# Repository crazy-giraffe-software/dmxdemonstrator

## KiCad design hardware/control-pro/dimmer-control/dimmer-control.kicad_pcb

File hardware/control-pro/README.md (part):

# DMX Demonstrator Control Pro  (DMX-CP*)

## Overview

The control-pro is built to work with either transmitter or transmitter-retro. When used with an Arduino, an additional board, the DMX-TX2, is required to connect the control-pro to the Arduino. The transmitter software automatically detects whether DMX-TX1, the standard transmitter, or DMX-TX2, the control-pro adapter, is connected.

The control pro is designed so that a series of components are sandwiched between 2 circuit boards. As a result, the heights of the components are fairly sensitive in order to make things line up nicely. Here are the parts for which I designed. The DMX-CPDB and DMX-CPCB boards contains all the parts and are the bottom of the sandwich, the DMX-CPDF and DMX-CPCB are the faceplate, i.e. the tops of the sandwich. If you are wondering why there are 4 total boards, see _PCB->Quality vs Price_ below.

## Online parts list

Sparkfun offers some, but not all, of the components required for the Control Pro. For the parts they can supply, you can find a parts lists [here](https://www.sparkfun.com/wish_lists/160543).

Additionally, you'll need some parts from the common parts lists as well. You can find the common parts list [here](https://www.sparkfun.com/wish_lists/160406). The rainbow LED pack include 2 sets of LED so if you are building more than 2 transmitters or receivers, make sure to buy 1 pack for every 2 transmitters/receivers.

## PCB

You can order the PCBs from [OHS Park](https://oshpark.com/):

- [Clock Control: DMX-CPCB 1.3](https://oshpark.com/shared_projects/???)
- [Clock Faceplate: DMX-CPCF 1.3](https://oshpark.com/shared_projects/???)
- [Dimmer Control: DMX-CPDB 1.3](https://oshpark.com/shared_projects/???)
- [Dimmer Faceplate: DMX-CPDF 1.3](https://oshpark.com/shared_projects/???)

### Quality vs Price

While it is counterintuitive (and in some cases wrong), splitting the clock controls and dimmer controls on different boards reduces cost. Many PCB manufacturers offer a fixed cost for board smaller than a certain size. These boards are 100mm x 100mm, which is standard max size for many low-cost board manufacturers. Others like OHSPark charge by the square inch and therefore the separate control approach is more expensive. Rev 1.1 was a single set of boards 180mm x 90mm for which OHSPark charges about $250US for 3 copies of both boards. Rev 1.3 is more expensive from OHSPark but can be as cheap as $20US for 5 copies of all 4 boards from cheaper board manufacturers. Yes, there is a quality BIG difference between those prices but the cheaper board will work just fine.

OHSPark offers really great quality at great prices, they are easy to work with, manufacture 100% in the US, and their support is excellent. I use OHSPark for almost everything I build, expect when the cost is super high. Lower cost boards can be had but if you spec the same quality board OHSPark offers at those places, you will find OHSPark to be competitive. Yes, the links above are for the more expensive OHSPark board for the reason I listed above plus ease of use: You can upload the file directly from Kicad and they can produce a board. Better yet, they will save that board for others to order. They make it so easy to order for a project like this it's silly not to use them.

I offer this opinion freely and do not receive any compensation from OHSPark.

## Parts

The Control Pro is designed so that a series of components are sandwiched between 2 circuit boards. As a result, the heights of the components are fairly sensitive in order to make things line up nicely. Here are the parts for which I designed. The DMX-CPDB and DMX-CPCB boards contains all the parts and are the bottom of the sandwich, the DMX-CPDF and DMX-CPCB are the faceplate, i.e. the tops of the sandwich. If you are wondering why there are 4 total boards, see _PCB->Quality vs Price_.

### Slider Potentiometers

Getting a potentiometer and knob combo that would work with the rest of the components was probably the hardest part of part selection.
I had initially ordered some 60mm 10k sliders from SparkFun with matching knobs and they measures about 25mm from the bottom of the
part to the bottom of the knob, which is way too tall for the other components! I landed on a combination of Bourns PTA Series
sliders with an knob available from Sparkfun (and others). During this process, I opted for a 45mm travel to keep the board smaller/cheaper
while still offering good mechanical resolution. The specific parts I designed for are:

- Dimmer Sliders: Bournes PTA4543-2015DPB103, quantity 4:
  - [Data sheet](https://www.mouser.com/datasheet/2/54/pta-778345.pdf)
  - [Digikey PTA4543-2015DPB103-ND](https://www.digikey.com/products/en?keywords=PTA4543-2015DPB103-ND)
  - [Mouser 652-PTA45432015DPB10](https://www.mouser.com/ProductDetail/Bourns/PTA4543-2015DPB103?qs=U%2FacTlguYxbmwS%2FtylIWJw%3D%3D)
- Knobs: Eagle 450-3051, quantity 4:
  - [Datasheet](https://www.mouser.com/datasheet/2/209/EPD-200140-1171100.pdf)
  - [Mouser 450-3051](https://www.mouser.com/ProductDetail/Eagle-Plastic-Devices/450-3051?qs=hTs5c5NaUrTeABpuQnP9ug%3D%3D)
  - [Sparkfun COM-09120](https://www.sparkfun.com/products/9120) - Included in online parts list

### Toggle Switches

Just about any miniature toggle switch will do, many manufacturers make a switch in a similar size. I specifically used the E-Switch Series 100 Miniature Toggle Switches, specifically:

- Clock Speed: E-Switch 100DP3T1B1M1QEH, quantity 1:
  - [Datasheet](https://sten-eswitch-13110800-production.s3.amazonaws.com/system/asset/product_line/data_sheet/129/100.pdf)
  - [Digikey EG2413-ND](https://www.digikey.com/products/en?keywords=100DP3T1B1M1QEH)
  - [Mouser 612-100-H1111](https://www.mouser.com/ProductDetail/E-Switch/100DP3T1B1M1QEH?qs=g8hxKYs5b3yy1L1GZVrx5w%3D%3D)
- Clock Step: E-Switch 100SP2T1B1M1QEH, quantity 1:
  - [Datasheet](https://sten-eswitch-13110800-production.s3.amazonaws.com/system/asset/product_line/data_sheet/129/100.pdf)
  - [Digikey EG2373-ND](https://www.digikey.com/product-detail/en/e-switch/100SP2T1B1M1QEH/EG2373-ND/378842)
  - [Mouser 612-100-B1111](https://www.mouser.com/ProductDetail/E-Switch/100SP2T1B1M1QEH?qs=HKd%2Fp3M7KlWCZ%252BGqDexPKQ%3D%3D)

### Rotary Potentiometer

With the toggle and sliders determining the basic component height, I searched for a rotary potentiometer to fit the requirements and once again found a Bournes product. It has a 6mm "D"/flattened shaft so just about any 6mm flattened shaft knob will work but something with a set screw will help secure it. I did not find a great choice at Digikey or Mouser but Amazon and EBay has a ton of choices, designed for use with musical instruments.

Sparkfun offers a potentiometer and knob that make an excellent choice. The knob even [goes to 11](https://en.wikipedia.org/wiki/Up_to_eleven). The Sparkfun part is not a Bournes PTV09A-4030F-B103 but it's the same physical size and resistance.

Specifically:

- Clock Speed Control: Bournes PTV09A-4030F-B103, quantity 1:
  - [Datasheet](https://www.bourns.com/docs/Product-Datasheets/PTV09.pdf)
  - [Digikey 118-PTV09A-4030F-B103-ND](https://www.digikey.com/en/products/detail/bourns-inc/PTV09A-4030F-B103/3820581)
  - [Mouser 652-PTV09A-4030FB103](https://www.mouser.com/ProductDetail/Bourns/PTV09A-4030F-B103?qs=Zq5ylnUbLm4pfFuWlwC80Q%3D%3D)
  - [Sparkfun COM-09288](https://www.sparkfun.com/products/9288) - Included in online parts list
- Knob, quantity 1:
  - [Sparkfun COM-11951](https://www.sparkfun.com/products/11951) - Included in online parts list

### LEDs and Spacers

Luckily most LEDs have leads long enough to make it from the bottom to top board so nothing special is needed here, just make sure to have 17.5mm of lead length. Most LEDs have a voltage and current range near 2v and 10ma and the design will accommodate variances easily.

I like the [Sparkfun rainbow LED Kit](https://www.sparkfun.com/products/12903) which gives you 2 each of 6 colors, letting you match colors for dimmers 1-4, data and clock on both the transmitter and receiver without re-using colors. This LED kit is included in the common parts list. However, they will need a bit of added stability, which is where an LED spacer is needed. Something between 16mm and 17mm will work fine. Here's a suitable one:

- LED: T1 3/4 or 5mm Led in various colors, quantity 1:
  - [Sparkfun rainbow LED Kit](https://www.sparkfun.com/products/12903) - Included in common online parts list
- LED Spacer: Würth 705820170, quantity 8:
  - [Data sheet](https://www.we-online.de/katalog/datasheet/705820xxx_overview.pdf)
  - [Digikey 732-11617-ND](https://www.digikey.com/product-detail/en/w%C3%BCrth-elektronik/705820170/732-11617-ND/7681962)
  - [Mouser 710-705820170](https://www.mouser.com/ProductDetail/Wurth-Elektronik/705820170?qs=wr8lucFkNMUaK6Cwpwjx5Q%3D%3D)

The rainbow LED kit includes 1 red and one green LED for the data and clock. However, there are 3 sets of data and clock LEDs on the three boards. Also, there are 2 LEDs to verify detection of the control-pro, one on each board. These LEDs are included in the control-pro online parts list [here](https://www.sparkfun.com/wish_lists/160543).

### Cable and Connector

To connect the controller to the transmitter, you'll need some cables and connectors. Ribbon cable makes a nice choice for this and you can find pre-made ribbon cable assemblies on Amazon and EBay easily. I've designed for a 16 pin cable. I recommend shrouded headers for connecting to PCBs and it ensures you don't plug the cable in backwards. Here are some suitable headers:

- Header: Würth Elektronik 61201621721, quantity 4:
  - [Datasheet](https://www.we-online.com/components/products/datasheet/61201621721.pdf)
  - [Digikey 732-2099-ND](https://www.digikey.com/en/products/detail/w%C3%BCrth-elektronik/61201621721/2060595)
  - [Mouser 710-61201621721](https://www.mouser.com/ProductDetail/Wurth-Elektronik/61201621721?qs=ZtY9WdtwX56ShT0tAQh3qw%3D%3D)
- Header: 3M 30316-6002HB, quantity 1:
  - [Datasheet](https://www.mouser.com/datasheet/2/1/78-5100-0818-4_D-221281.pdf)
  - [Digikey 3M11931-ND](https://www.digikey.com/products/en?keywords=30316-6002HB)
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
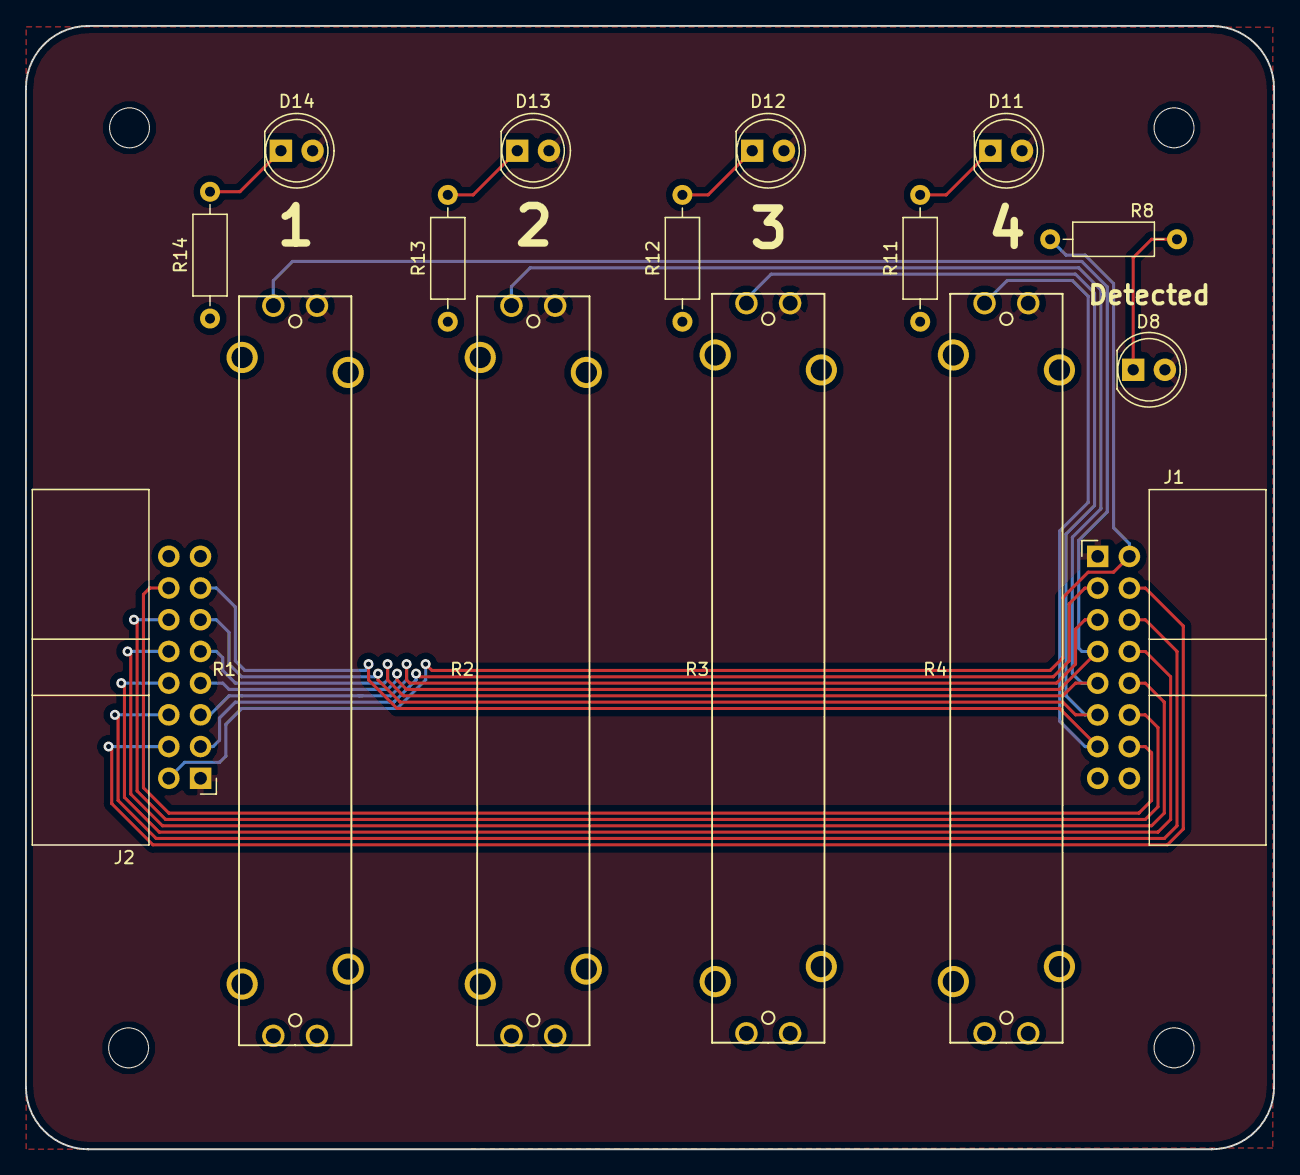
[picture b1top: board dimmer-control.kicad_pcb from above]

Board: 2 copper layers, 100.0 x 90.0 mm, 20 parts (0 on the bottom side), 20 nets.

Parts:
D8: LED; LED_D5.0mm
D11: DIM4; LED_D5.0mm
D12: DIM3; LED_D5.0mm
D13: DIM2; LED_D5.0mm
D14: DIM1; LED_D5.0mm
J1: OUTPUT; IDC-Header_2x08_P2.54mm_Horizontal
J2: INPUT; IDC-Header_2x08_P2.54mm_Horizontal
MH1, MH2, MH3, MH4: MountingHole; MountingHole_3.2mm_M3
R1, R2, R3, R4: 10k; BOURNS_PTA4543
R8, R11, R12, R13, R14: 330; R_Axial_DIN0207_L6.3mm_D2.5mm_P10.16mm_Horizontal

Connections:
+5V: D8.2, D11.2, D12.2, D13.2, D14.2, J1.1, J2.1, R1.1, R2.1, R3.1, R4.1
/DIM1: J1.7, J2.7, R1.2
/DIM2: J1.9, J2.9, R2.2
/DIM3: J1.11, J2.11, R3.2
/DIM4: J1.13, J2.13, R4.2
/SPD_HI: J1.4, J2.4
/SPD_LO: J1.8, J2.8
/SPD_WIPER: J1.6, J2.6
/~CLK_FST: J1.14, J2.14
/~CLK_SLO: J1.12, J2.12
/~CLK_STEP: J1.10, J2.10
/~CLOCK: J1.3, J2.3
/~DATA: J1.5, J2.5
/~HWD_DT: J1.2, J2.2, R8.1
GND: J1.15, J1.16, J2.15, J2.16, R1.3, R2.3, R3.3, R4.3, R11.1, R12.1, R13.1, R14.1
unnamed: D8.1, R8.2
unnamed: D11.1, R11.2
unnamed: D12.1, R12.2
unnamed: D13.1, R13.2
unnamed: D14.1, R14.2

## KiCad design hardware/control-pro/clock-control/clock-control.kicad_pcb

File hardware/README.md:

# DMX Demonstrator Hardware

## Overview

The DMX Demonstrator hardware folder contains various transmitters, receivers, and modules which all for the control of brightness of 4 channels of dimming.

## Status

Each hardware folder will contain a readme explaining the details of the component and it's status. The following is a definition of some common status:

- 

The _verified_ badge indicates that the component has been built and tested for use with the DMX Demonstrator family and is safe to build.

- 

The _testing_ badge indicates that the component has completed the design and prototype phase and being verified for use with the DMX Demonstrator family. It usually is assigned to a component revision for which the previous version is _verified_.

- 

The _prototype_ badge indicates that the component has completed the design phase and is being built and tested for use with the DMX Demonstrator family.

- 

The _design_ badge indicates that the component is still being design. has completed the design phase.

## Compatibility

For the components which connect to an Arduino, the readme provides a list of known compatible Arduino platforms. The DMX Demonstrator family will likely work with most Arduino boards, real or clones, but if you are having an
[issue](https://github.com/crazy-giraffe-software/dmxdemonstrator/issues) with a particular board, open an issue to ask for verification. Please provide as much detail on the board and where is was obtained as possible.

The following is a definition of some compatibilities:

- 

The _verified_ badge indicates that the component has been built and tested for the specific Arduino board.

- 

The _testing_ badge indicates that the component is being tested to determine if it is compatible with the specific Arduino board.

- 

The _research_ badge indicates that the component is being researched to determine if it is compatible with the specific Arduino board.

- 

The _incompatible_ badge indicates that the component is not compatible for the specific Arduino board.

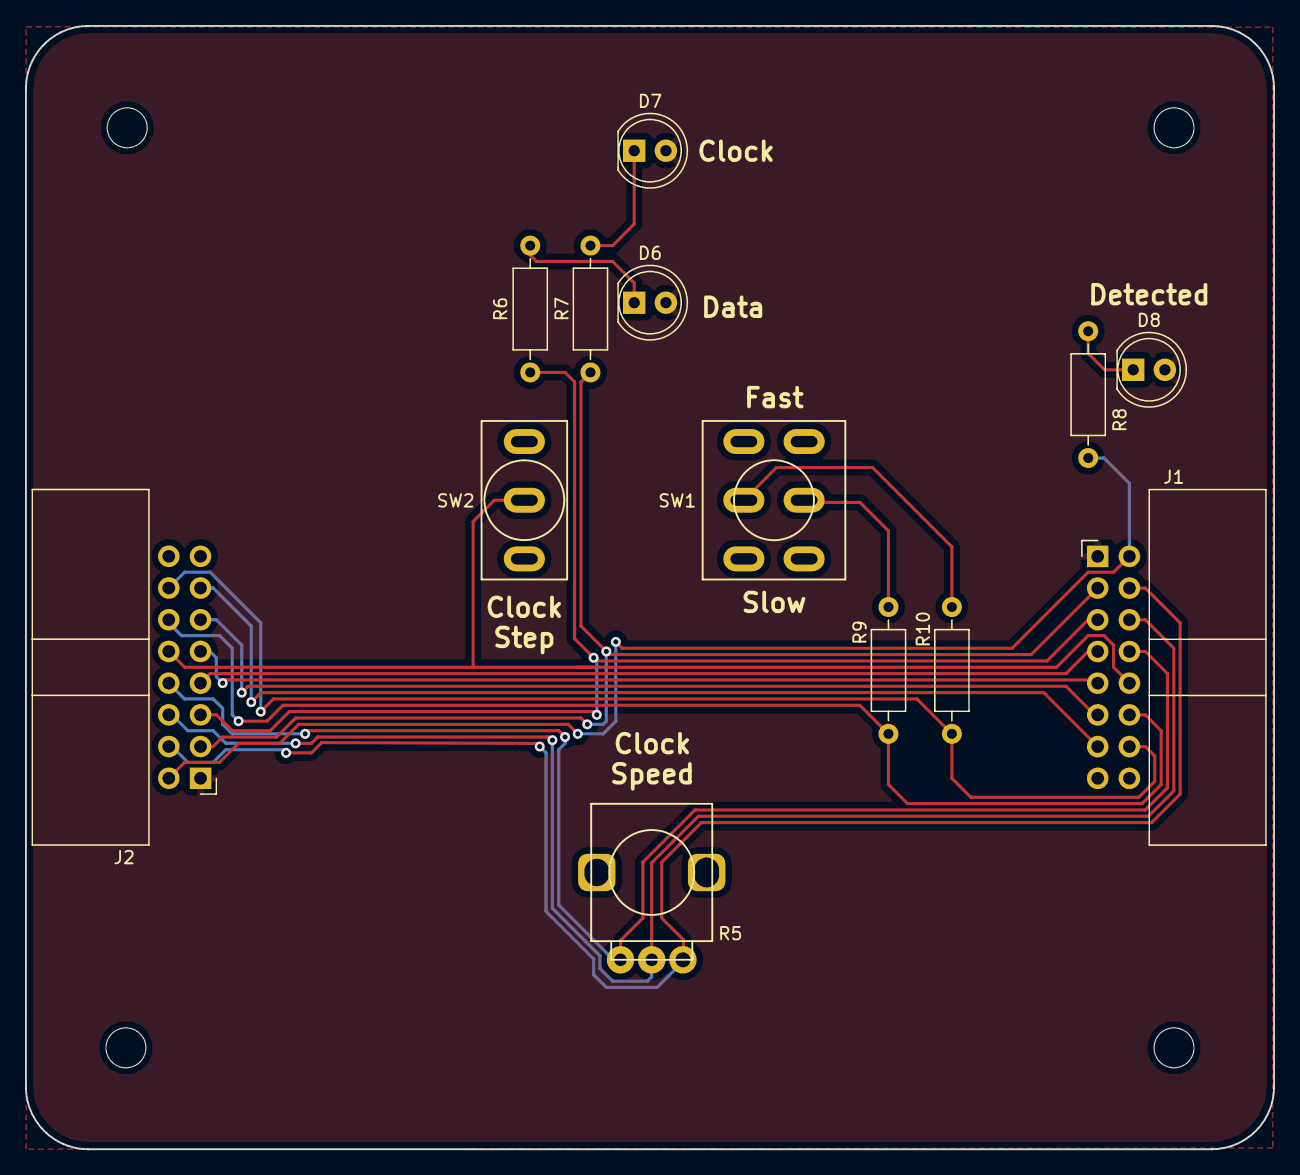
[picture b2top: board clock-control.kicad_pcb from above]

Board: 2 copper layers, 100.0 x 90.0 mm, 17 parts (0 on the bottom side), 20 nets.

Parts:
D6: DATA; LED_D5.0mm
D7: CLOCK; LED_D5.0mm
D8: ACTIVE; LED_D5.0mm
J1: OUTPUT; IDC-Header_2x08_P2.54mm_Horizontal
J2: INPUT; IDC-Header_2x08_P2.54mm_Horizontal
MH1, MH2, MH3, MH4: MountingHole; MountingHole_3.2mm_M3
R5: 10k; BOURNS_PTV09A_1
R6, R7, R8, R9, R10: 330; R_Axial_DIN0207_L6.3mm_D2.5mm_P10.16mm_Horizontal
SW1: CLOCK_SPEED; ESWITCH_100_DPDT_M1
SW2: CLOCK_STEP; ESWITCH_100_SPDT_M1

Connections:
+5V: D6.2, D7.2, D8.2, J1.1, J2.1
/DIM1: J1.7, J2.7
/DIM2: J1.9, J2.9
/DIM3: J1.11, J2.11
/DIM4: J1.13, J2.13
/SPD_HI: J1.4, J2.4, R5.3
/SPD_LO: J1.8, J2.8, R5.1
/SPD_WIPER: J1.6, J2.6, R5.2
/~CLK_FST: J1.14, J2.14, R10.1
/~CLK_SLO: J1.12, J2.12, R9.1
/~CLK_STEP: J1.10, J2.10, SW2.2
/~CLOCK: J1.3, J2.3, R7.1
/~DATA: J1.5, J2.5, R6.1
/~HWD_DT: J1.2, J2.2, R8.1
GND: J1.15, J1.16, J2.15, J2.16, SW1.3, SW1.4, SW2.3
unnamed: D6.1, R6.2
unnamed: D7.1, R7.2
unnamed: D8.1, R8.2
unnamed: R9.2, SW1.2
unnamed: R10.2, SW1.5

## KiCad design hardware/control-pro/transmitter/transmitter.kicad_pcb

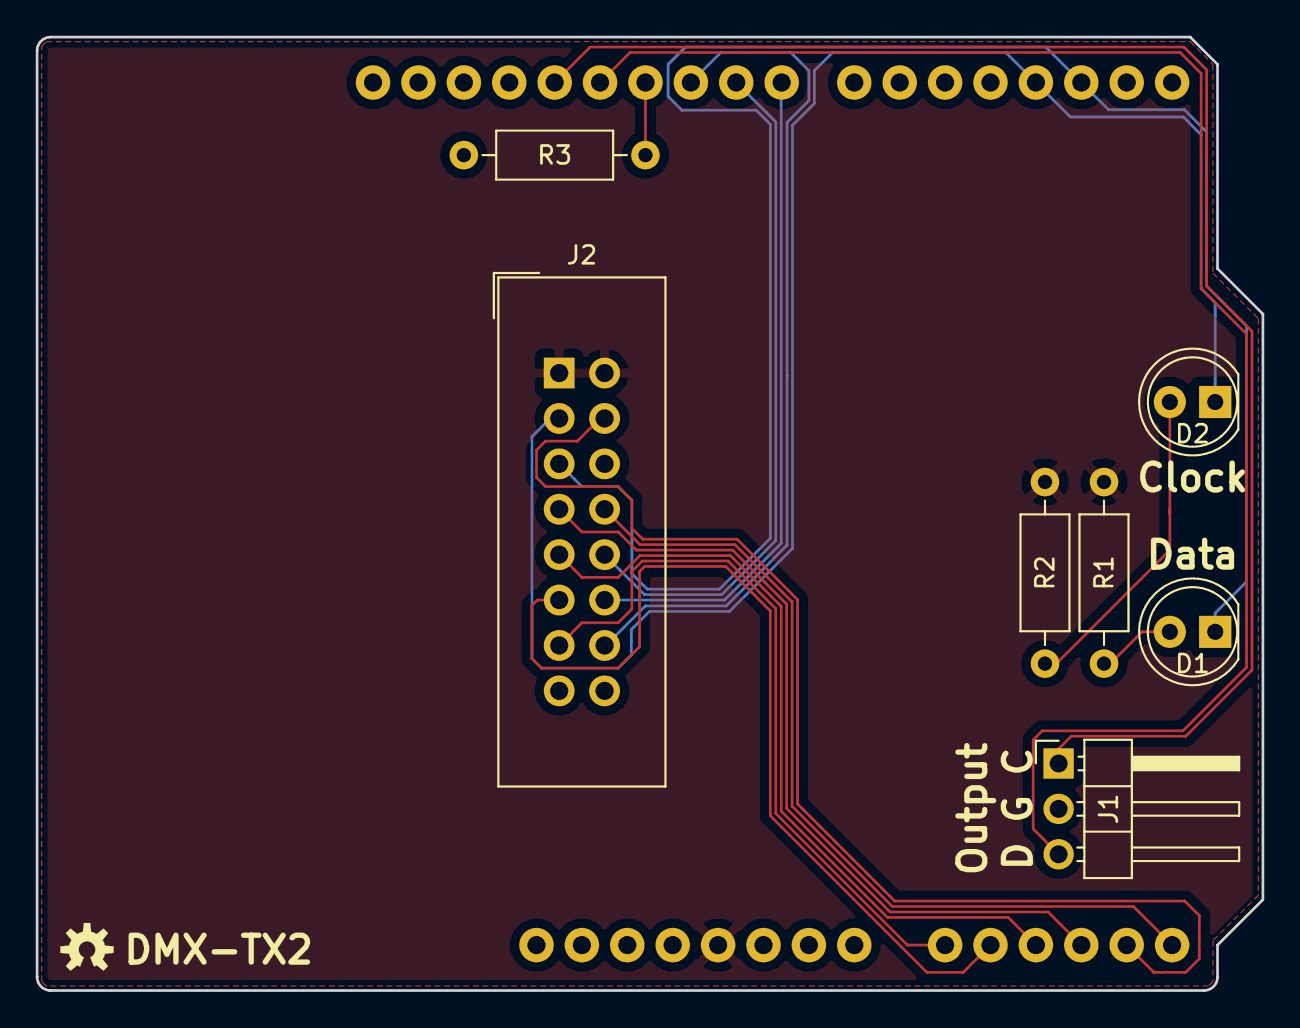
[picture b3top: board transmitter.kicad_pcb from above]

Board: 2 copper layers, 68.6 x 53.3 mm, 8 parts (0 on the bottom side), 18 nets.

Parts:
A1: Arduino_UNO_R3; ARDUINO_R3_NO_HOLES
D1: DATA; LED_D5.0mm
D2: CLOCK; LED_D5.0mm
J1: Output; PinHeader_1x03_P2.54mm_Horizontal
J2: INPUT; IDC-Header_2x08_P2.54mm_Vertical
R1, R2, R3: 330; R_Axial_DIN0207_L6.3mm_D2.5mm_P10.16mm_Horizontal

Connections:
+5V: A1.5, J2.1, J2.2, R1.1, R2.1
/A0: A1.9, J2.13
/A1: A1.10, J2.11
/A2: A1.11, J2.9
/A3: A1.12, J2.7
/A4: A1.13, J2.4
/A5: A1.14, J2.8
/RX: A1.27, J1.3
/RXCLK: A1.28, J1.1
/~CLK_FST: A1.23, J2.12
/~CLK_SLO: A1.24, J2.10
/~CLOCK: A1.18, D2.1, J2.3
/~DATA: A1.17, D1.1, J2.5
/~HWD_DT: A1.25, J2.14
GND: A1.6, A1.7, A1.29, J1.2, J2.6, J2.15, J2.16, R3.2
unnamed: A1.26, R3.1
unnamed: D1.2, R1.2
unnamed: D2.2, R2.2

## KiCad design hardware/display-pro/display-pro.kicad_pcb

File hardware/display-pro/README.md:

# DMX Demonstrator Display-Pro (DMX-DSP)

## Overview

The display-pro is stand-along module which intercepts the 3-wire data/clock signal from the transmitter to amplify the data and clock signals and drive a larger display intended for a large audience.

It is built to drive an DC output for up to 60v volts so it is compatible with a variety of displays. The parts list has a display and power supply to keep you from having to come up with your own. Feel free to use the recommended option or play around with something else.

## Online parts list

Sparkfun offers all of the components required for the display-pro. You can find a parts lists [here](https://www.sparkfun.com/wish_lists/160583).

If you plan to use something else for the display, you can leave out the Big Dome Buttons, the 12v power supply (you'll likely need something to supply more current anyway). You may also want to consider adding heat sinks, either two of the [PRT-00121](https://www.sparkfun.com/products/121) or [PRT-14340](https://www.sparkfun.com/products/14340) depending on your load.

## PCB

You can order the PCB from [OHS Park](https://oshpark.com/):

- [DMX-DSP, Rev 1.3](https://oshpark.com/shared_projects/WQ5EMRMl).

## Version History

### Rev 1.4

- Switched power connector
- Fix current limiting resistors
- Remove load resistors
- Re-label ins and outs

### Rev 1.3

- Standard board to match IO modules

### Rev 1.2

- Remove COAX power connector

### Rev 1.1

- Added rounded corners

### Rev 1.0

- Initial draft

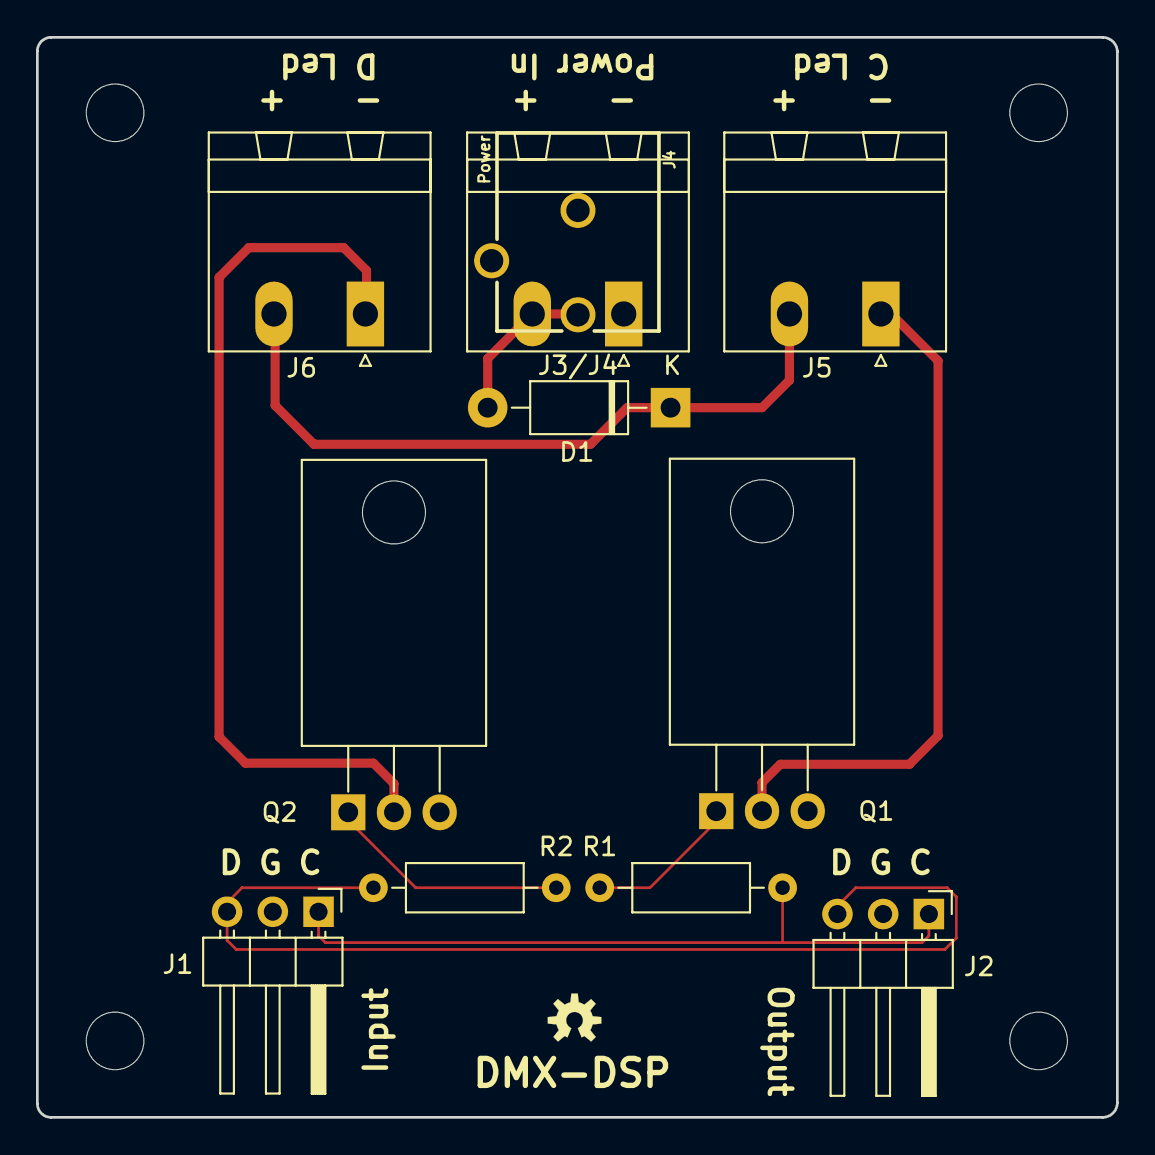
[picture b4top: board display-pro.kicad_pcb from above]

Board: 2 copper layers, 60.0 x 60.0 mm, 15 parts (0 on the bottom side), 9 nets.

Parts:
D1: 1N5819; D_DO-41_SOD81_P10.16mm_Horizontal
J1: Input; PinHeader_1x03_P2.54mm_Horizontal
J2: Output; PinHeader_1x03_P2.54mm_Horizontal
J3: Power; PhoenixContact_MSTBA_2,5_2-G-5,08_1x02_P5.08mm_Horizontal
J4: Power; POWER_JACK_PTH_BREAD
J5: C Out; PhoenixContact_MSTBA_2,5_2-G-5,08_1x02_P5.08mm_Horizontal
J6: D Out; PhoenixContact_MSTBA_2,5_2-G-5,08_1x02_P5.08mm_Horizontal
MH1, MH2, MH3, MH4: MountingHole; MountingHole_3.2mm_M3
Q1, Q2: FQP30N06L; TO-220-3_Horizontal_TabDown
R1, R2: 10k; R_Axial_DIN0207_L6.3mm_D2.5mm_P10.16mm_Horizontal

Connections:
+VDC: D1.1, J5.2, J6.2
/C: J1.1, J2.1, R1.2
/D: J1.3, J2.3, R2.2
GND: J1.2, J2.2, J3.1, J4.GND, J4.GNDB, Q1.3, Q2.3
unnamed: D1.2, J3.2, J4.PWR
unnamed: J5.1, Q1.2
unnamed: J6.1, Q2.2
unnamed: Q1.1, R1.1
unnamed: Q2.1, R2.1

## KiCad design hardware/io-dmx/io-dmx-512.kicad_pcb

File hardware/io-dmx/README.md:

# DMX Demonstrator DMX-512 IO Module (DMX-IO1)

## Overview

The DMX-512 IO Module is a stand-alone module which generates or receives a DMX-512 signal,allowing the DMS Demonstrator system to communicate with DMX-512-compatible and RDM-compatible equipment. It can be used with a Receiver (DMX-RX2, DMX-RX?) to receive DMX-512. It can also be used with a Transmitter (DMX-TX2, DMX-TX?) to transmit the data stream to DMX-512.

## Online parts list

Sadly, Sparkfun does not offer all of the components required for DMX-512 IO Module. Additionally, Digikey does not carry Neutrik for connecting
to the DMX/RDM devices.

The parts can be purchased from [Mouser](https://www.mouser.com/) or [Newark](https://www.newark.com/). Links and part numbers are listed below.

- U5, MAX3485CPA+ -
[Newark 81Y9431](https://www.newark.com/maxim-integrated-products/max3485cpa/rs422-rs485-transceiver-10mbps/dp/81Y9431?st=max3485)
[Mouser 700-MAX3485CPA](https://www.mouser.com/ProductDetail/Maxim-Integrated/MAX3485CPA%2b/?qs=LHmEVA8xxfbU8x9nGoNB%2Fw%3D%3D)
[MAX3485 Datasheet](https://www.mouser.com/datasheet/2/256/MAX3483_MAX3491-1292143.pdf)

- C2-C5, 0.1uF -
[Newark 13K6284](https://www.newark.com/kemet/c315c104m5u5ta/capacitor-mlcc-z5u-100nf-50v-radial/dp/39K6432)
[Mouser 80-C320C104K5R7301](https://www.mouser.com/ProductDetail/KEMET/C320C104K5R5TA7301/?qs=cWONFOU2MXytiO%2Fz22pl%252Bg%3D%3D)
[Sparkfun 8375](https://www.sparkfun.com/products/8375)

- R5-10, 470 ohm -
[Newark 38K0375](https://www.newark.com/multicomp-pro/mcf-0-25w-470r/carbon-film-resistor-470-ohm-250mw/dp/38K0375)
[Mouser 603-CFR-25JT-52-470R](https://www.mouser.com/ProductDetail/Yageo/CFR-25JT-52-470R/?qs=sGAEpiMZZMtlubZbdhIBIFoOGUvNp40adtovOrQ4BzA%3D)

- R11 & R13, 680 ohm -
[Newark 38K0387](https://www.newark.com/multicomp-pro/mcf-0-25w-680r/carbon-film-resistor-680-ohm-250mw/dp/38K0387)
[Mouser 603-CFR-25JB-52-680R](https://www.mouser.com/ProductDetail/Yageo/CFR-25JB-52-680R/?qs=sGAEpiMZZMtlubZbdhIBINt%2Ft6Hry3%2FBZYYRBIijkE4%3D)

- R12 - 120 ohm -
[Newark 38K0333](https://www.newark.com/multicomp-pro/mcf-0-25w-120r/carbon-film-resistor-120-ohm-250mw/dp/38K0333)
[Mouser 603-CFR-25JT-52-120R](https://www.mouser.com/ProductDetail/Yageo/CFR-25JT-52-120R/?qs=sGAEpiMZZMtlubZbdhIBIFoOGUvNp40ae6q2awCfJoc%3D)

Additionally, you'll need some parts from the common parts lists as well. You can find the common parts list [here](https://www.sparkfun.com/wish_lists/160406).

- D1-D4
- J1
- R1-R4

### DMX Connectors

As you know, DMX commonly uses a 5-pin XLR connector. However, it is sometimes used with a 3-pin XLR connector which does not comply with the USITT spec. I'm not a fan of the 3-pin variant since it is the same as the audio connector making it seem as if DMX-512 and Mic cables can be used interchangeably, which they cannot reliably (your milage may vary).

That said, the DMX-IO1 supports both XLR-5 and XLR-3 connectors, one male and one female. You can choose between XLR-5 and XLR-3 but cannot use both at the same time. The design is made for Neutrik connectors (which is not a brand that Digikey carries). There are a few variation of the basic part numbers listed below with different shielding configurations. For instance, Newark only carries the NC3FAH-2, which works fine in place of the NC3FAH.

- 5-pin male XLR:
[Newark 25C4313](https://www.newark.com/neutrik/nc5mah/connector-xlr-audio-plug-5pos/dp/25C4313?ost=nc5mah)
[Mouser 568-NC5MAH](https://www.mouser.com/ProductDetail/Neutrik/NC5MAH/?qs=43pPWqpsSNtpdAMzqMXlkw%3D%3D)
[NC5MAH Datasheet](https://www.neutrik.com/en/product/nc5mah.pdf)

- 5-pin female XLR:
[Newark 94C1524](https://www.newark.com/neutrik/nc5fah/connector-xlr-receptacle-5-position/dp/94C1524?ost=nc5fah)
[Mouser 568-NC5FAH](https://www.mouser.com/ProductDetail/Neutrik/NC5FAH/?qs=JfNPhaIww3Jo8umm7Mfi2w%3D%3D)
[NC5FAH Datasheet](https://www.neutrik.com/en/product/nc5fah.pdf)

- 3-pin male XLR:
[Newark 91F3468](https://www.newark.com/neutrik/nc3mah/connector-xlr-plug-3-position/dp/91F3468?st=nc3mah)
[Mouser 568-NC3MAH](https://www.mouser.com/ProductDetail/Neutrik/NC3MAH/?qs=MO8z%252B%252BLepAHrH1t47qrfbA%3D%3D)
[NC3MAH Datasheet](https://www.neutrik.com/en/product/nc3mah.pdf)

- 3-pin female XLR:
[Newark 27B4208](https://www.newark.com/neutrik/nc3fah2/connector-xlr-audio-rcpt-3pos/dp/27B4208)
[Mouser 568-NC3FAH](https://www.mouser.com/ProductDetail/Neutrik/NC3FAH/?qs=43pPWqpsSNse2FCN7qQVQw%3D%3D)
[NC3FAH-0 Datasheet](https://www.neutrik.com/en/product/nc3fah-0.pdf)

### Isolation

There are a few different DMX Arduino shields but many of them do not have isolation as recommended by the USITT spec. The DMX-DD1 shamelessly steals it's design from [SparkFun ESP32 Thing Plus DMX to LED Shield](https://www.sparkfun.com/products/15110) which properly implements isolation including power supply isolation. Isolation is implemented using the following parts:

- U1, NMA0505SC:
[Newark 61K3058](https://www.newark.com/murata-power-solutions/nma0505sc/dc-dc-converter-iso-pol-2-o-p/dp/61K3058?ost=nma0505sc)
[Mouser 580-NMA0505SC](https://www.mouser.com/ProductDetail/Murata-Power-Solutions/NMA0505SC/?qs=%2Fha2pyFaduhGNEy44F69mkKiigmHmVay9P4cLoAL7Ps%3D)
[NMA0505SC Datasheet](https://www.mouser.com/datasheet/2/281/kdc_nma-29224.pdf)

- U2-U4, 6N137:
[Newark 52M1895](https://www.newark.com/vishay/6n137/optocoupler-transistor-5300vrms/dp/52M1895?st=6n137)
[Mouser 782-6N137](https://www.mouser.com/ProductDetail/Vishay-Semiconductors/6N137/?qs=xCMk%252BIHWTZMrQz4FyDXhMg%3D%3D)
[6N137 Datasheet](https://www.mouser.com/datasheet/2/427/6n137-1767489.pdf)

You can use the DMX-IO1 without isolation by leaving out these parts and installing 5 solder bridges to bypass the isolation circuits:

- Under U1, you will find a pair of bypass pads for +5v
- Under U1, you will find a pair of bypass pads for GND
- Under U2, you will find a pair of bypass pads for RX
- Under U3, you will find a pair of bypass pads for DIR
- Under U4, you will find a pair of bypass pads for TX

## Version History

### Rev 1.2

- Switched to a stand-alone module

### Rev 1.1

- Moved DMX connectors
- Added bypass pads to U1

### Rev 1.0

- Initial draft

## Other Options

If you don't want to make a DMX-DD1, there are other DMX-compatible shields
which can work with the DMS demonstrator. Here are some other options:

- [DFRobot DMX Shield for Arduino](https://www.dfrobot.com/product-984.html)
- [mathertel.de DMX Shield for Arduino with isolation](http://www.mathertel.de/Arduino/DMXShield.aspx)
- [SK Pang Arduino DMX Shield](http://skpang.co.uk/catalog/arduino-dmx-shield-p-663.html)
- [Conceptinetics DMX Shield for Arduino (RDM Capable)](https://www.tindie.com/products/Conceptinetics/dmx-shield-for-arduino-rdm-capable/)
- [Conceptinetics 2.5kV Isolated DMX 512 Shield for Arduino - R2](https://www.tindie.com/products/Conceptinetics/25kv-isolated-dmx-512-shield-for-arduino-r2/?pt=full_prod_search)

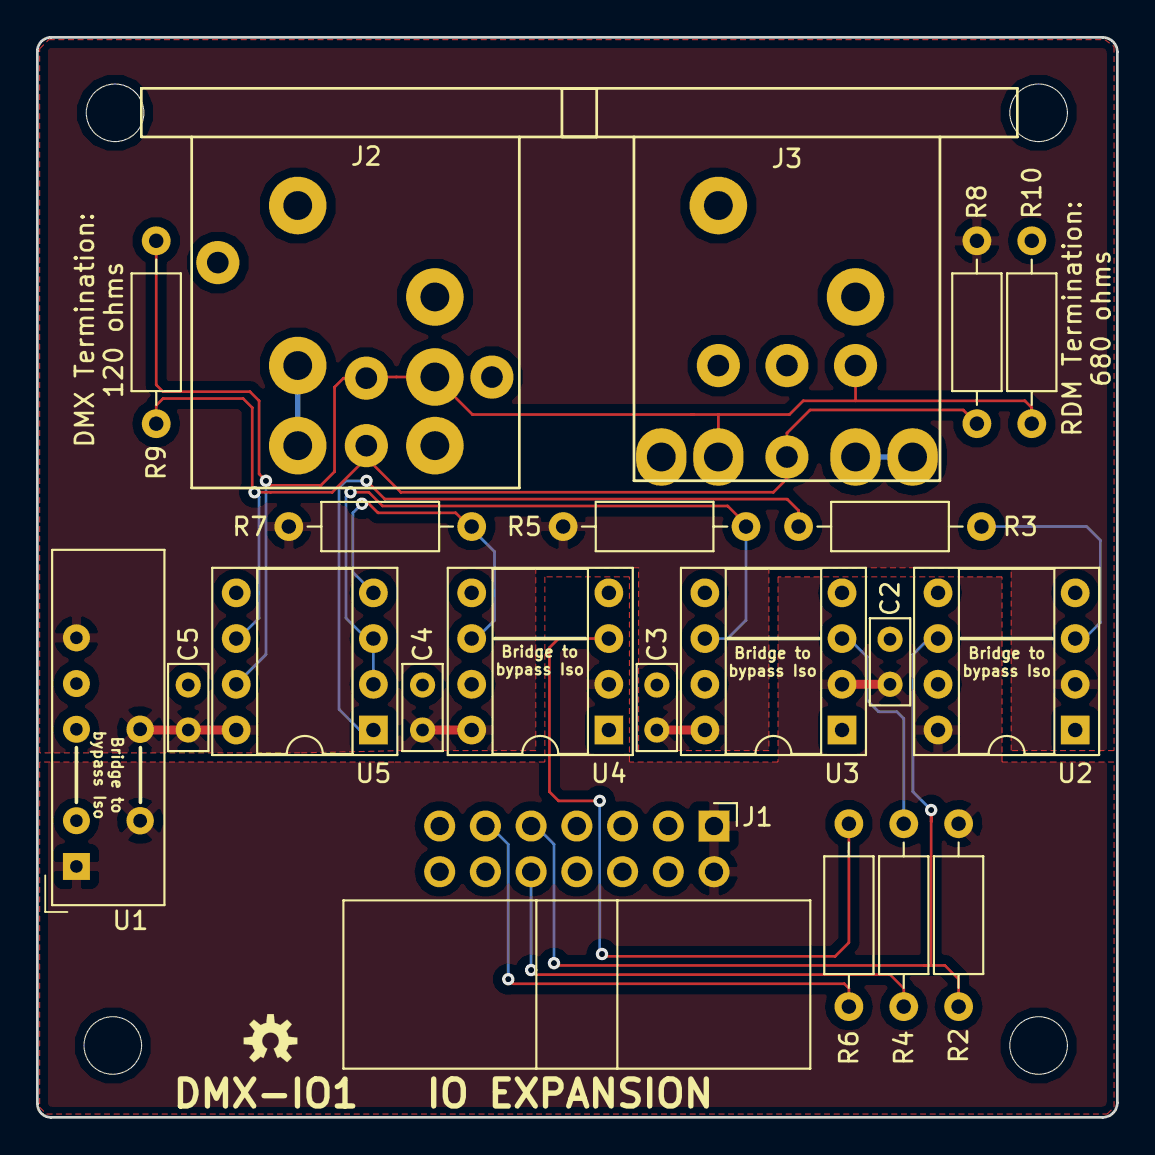
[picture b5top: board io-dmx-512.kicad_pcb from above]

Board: 2 copper layers, 60.0 x 60.0 mm, 25 parts (0 on the bottom side), 15 nets.

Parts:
C2, C3, C4, C5: .01uF; C_Rect_L4.6mm_W2.0mm_P2.50mm_MKS02_FKP02
J1: IO EXTENSION; IDC-Header_2x07_P2.54mm_Horizontal
J2: NC3FAH/NC5FAH; NEUTRIK-NC3FAH-NC5FAH
J3: NC3MAH/NC5MAH; NEUTRIK-NC3MAH-NC5MAH
MH1, MH2, MH3, MH4: MountingHole; MountingHole_3.2mm_M3
R2, R3, R4, R5, R6, R7: 470; R_Axial_DIN0207_L6.3mm_D2.5mm_P10.16mm_Horizontal
R8, R10: 680; R_Axial_DIN0207_L6.3mm_D2.5mm_P10.16mm_Horizontal
R9: 120; R_Axial_DIN0207_L6.3mm_D2.5mm_P10.16mm_Horizontal
U1: NMA0505SC; Converter_DCDC_muRata_NMAxxxxSC_THT_Bypass
U2, U3, U4: 6N137; DIP-8_W7.62mm_Socket
U5: MAX3485CPA+; DIP-8_W7.62mm_Socket

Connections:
+5V: C2.1, J1.1, J1.2, R2.1, U1.1, U2.8, U3.2, U4.2
/DMX-DIR: J1.10, R4.2
/DMX-RX: J1.9, R2.2, U2.6
/DMX-TX: J1.11, R6.2
GND: C2.2, J1.13, J1.14, U1.2, U2.5
GNDD: C3.2, C4.2, C5.2, J2.1A, J2.1B, J3.1A, J3.1B, R10.2, U1.4, U3.5, U4.5, U5.5
unnamed: J2.2A, J2.2B, J3.2A, J3.2B, R9.1, R10.1, U5.7
unnamed: J2.3, J3.3, R8.1, R9.2, U5.6
unnamed: R3.1, U5.1
unnamed: R3.2, U2.3
unnamed: R4.1, U3.3
unnamed: R5.1, U3.6, U5.2, U5.3
unnamed: R6.1, U4.3
unnamed: R7.1, U4.6, U5.4
VDD: C3.1, C4.1, C5.1, R5.2, R7.2, R8.2, U1.6, U2.2, U3.8, U4.8, U5.8

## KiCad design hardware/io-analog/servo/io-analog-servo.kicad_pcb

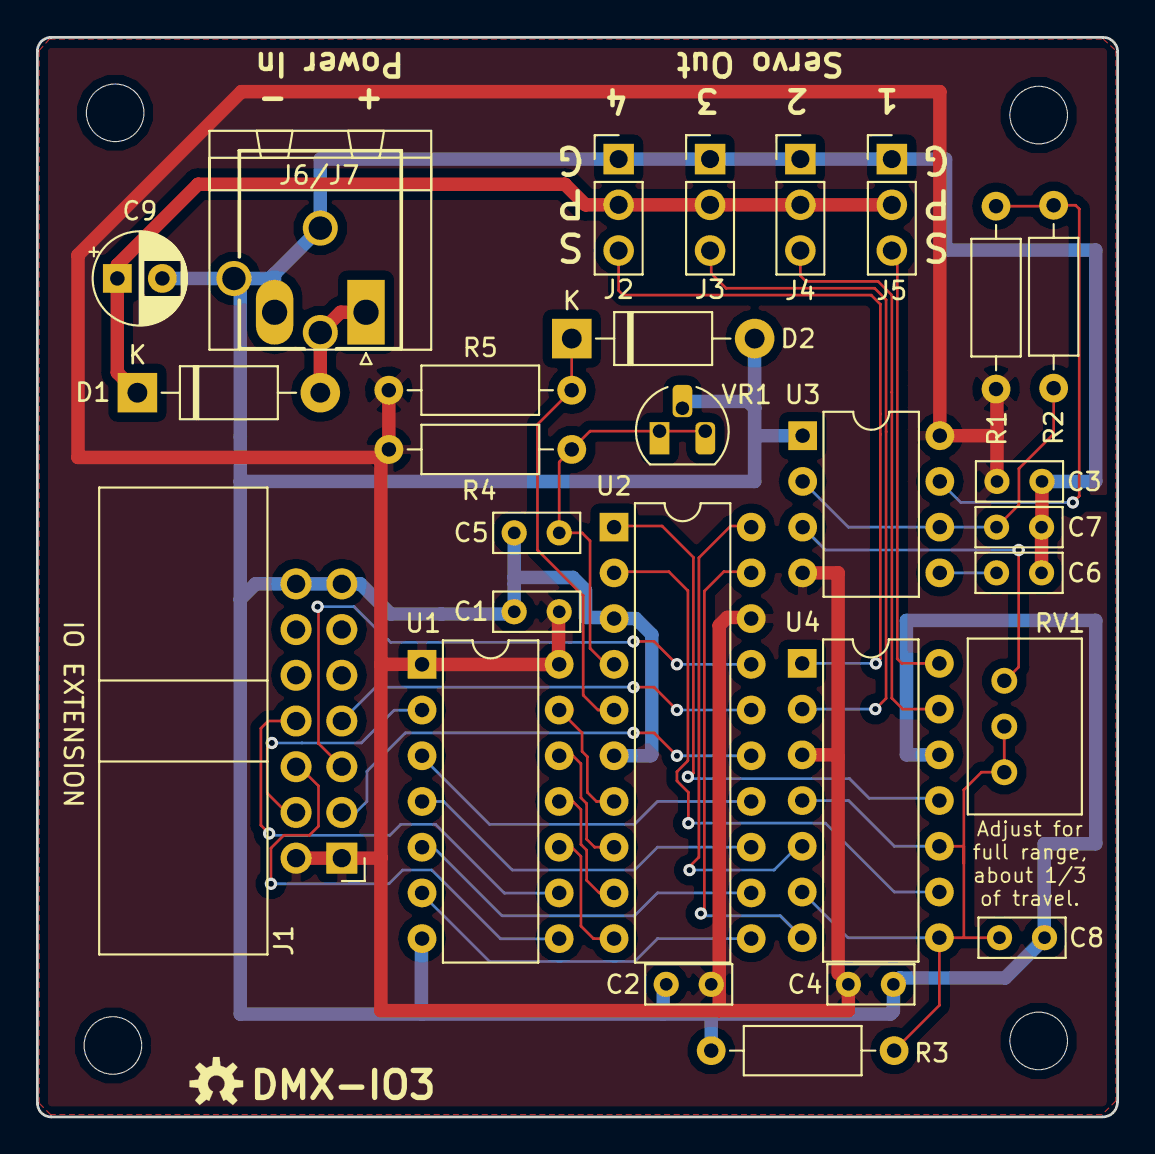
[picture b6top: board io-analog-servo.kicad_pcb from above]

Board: 2 copper layers, 60.0 x 60.0 mm, 33 parts (0 on the bottom side), 33 nets.

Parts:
C1, C2, C3, C4, C5: .01uF; C_Rect_L4.6mm_W2.0mm_P2.50mm_MKS02_FKP02
C6: 100nf; C_Rect_L4.6mm_W2.0mm_P2.50mm_MKS02_FKP02
C7, C8: 0.68uF; C_Rect_L4.6mm_W2.0mm_P2.50mm_MKS02_FKP02
C9: 10uF; CP_Radial_D5.0mm_P2.50mm
D1: 1N5819; D_DO-41_SOD81_P10.16mm_Horizontal
D2: D; D_DO-41_SOD81_P10.16mm_Horizontal
J1: IO Extension; IDC-Header_2x07_P2.54mm_Horizontal
J2: Servo3; PinHeader_1x03_P2.54mm_Vertical
J3: Servo2; PinHeader_1x03_P2.54mm_Vertical
J4: Servo1; PinHeader_1x03_P2.54mm_Vertical
J5: Servo0; PinHeader_1x03_P2.54mm_Vertical
J6: Power; PhoenixContact_MSTBA_2,5_2-G-5,08_1x02_P5.08mm_Horizontal
J7: Power; POWER_JACK_PTH_BREAD
MH1, MH2, MH3, MH4: MountingHole; MountingHole_3.2mm_M3
R1: 330; R_Axial_DIN0207_L6.3mm_D2.5mm_P10.16mm_Horizontal
R2, R3: 10k; R_Axial_DIN0207_L6.3mm_D2.5mm_P10.16mm_Horizontal
R4: 1.6k; R_Axial_DIN0207_L6.3mm_D2.5mm_P10.16mm_Horizontal
R5: R_US; R_Axial_DIN0207_L6.3mm_D2.5mm_P10.16mm_Horizontal
RV1: 10k; Potentiometer_Bourns_3299W_Vertical
U1: 74LS164; DIP-14_W7.62mm
U2: TLC7226A; DIP-20_W7.62mm
U3: LM555; DIP-8_W7.62mm
U4: LM339; DIP-14_W7.62mm
VR1: TL1431; TO-92L_HandSolder

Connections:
+2V5: C5.1, R4.1, U2.4, VR1.1, VR1.3
+5V: C1.1, C2.1, C3.1, C4.1, J1.1, J1.2, R1.1, R4.2, R5.1, U1.1, U1.14, U2.18, U3.4, U3.8, U4.3
/A0: J1.5, U2.17
/A1: J1.7, U2.16
/AO0: U2.2, U4.9
/AO1: U2.1, U4.11
/AO2: U2.20, U4.5
/AO3: U2.19, U4.7
/D0: U1.3, U2.14
/D1: U1.4, U2.13
/D2: U1.5, U2.12
/D3: U1.6, U2.11
/D4: U1.10, U2.10
/D5: U1.11, U2.9
/D6: U1.12, U2.8
/D7: U1.13, U2.7
/SR-CLK: J1.6, U1.8
/SR-OUT: J1.4, U1.2
/~SR_CLR: J1.8, U1.9
/~WR: J1.3, U2.15
GND: C1.2, C2.2, C3.2, C4.2, C5.2, C6.1, C7.1, C8.2, C9.2, D2.2, J1.13, J1.14, J2.1, J3.1, J4.1, J5.1, J6.2, J7.GND, J7.GNDB, R3.1, U1.7, U2.3, U2.6, U3.1, U4.12, VR1.2
unnamed: C6.2, U3.5
unnamed: C7.2, R2.2, U3.2, U3.6
unnamed: C8.1, R3.2, RV1.2, RV1.3, U4.4, U4.6, U4.8, U4.10
unnamed: C9.1, D1.1, J2.2, J3.2, J4.2, J5.2
unnamed: D1.2, J6.1, J7.PWR
unnamed: D2.1, R5.2, U2.5
unnamed: J2.3, U4.1
unnamed: J3.3, U4.2
unnamed: J4.3, U4.13
unnamed: J5.3, U4.14
unnamed: R1.2, R2.1, U3.7
unnamed: RV1.1, U3.3

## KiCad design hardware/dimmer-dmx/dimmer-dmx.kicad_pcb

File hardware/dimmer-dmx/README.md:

# DMX Demonstrator DMX Dimmer (DMX-DD1)

## Overview

The digital dimmer is...

## DMX Connectors

Of course DMX commonly uses a 5-pin XLR, it is often used with a 3-pin XLR. I'm not a fan of the 3-pin variant since it is the same as the audio connector making it seem as if DMX and Mic cables can be used interchangeably.

That said, the DMX-DD1 supports both XLR-5 and XLR-3 connectors, one male and one female. You can choose between XLR-5 and XLR-3 but cannot use both at the same time.

[Digikey 1937-1150-ND](https://www.digikey.com/product-detail/en/io-audio-technologies/IO-XLR5-F-EH/1937-1150-ND/9931892)
[Datasheet](https://ioaudiotech.com/engineering-drawings/IO-XLR5-X-EH.pdf)

[Digikey 1937-1149-ND](https://www.digikey.com/product-detail/en/io-audio-technologies/IO-XLR5-M-EH/1937-1149-ND/9931891)
[Datasheet](https://ioaudiotech.com/engineering-drawings/IO-XLR5-X-EH.pdf)

[Digikey 1937-1146-ND](https://www.digikey.com/product-detail/en/io-audio-technologies/IO-XLR3-F-EH/1937-1146-ND/9931888)
[Datasheet](https://ioaudiotech.com/engineering-drawings/IO-XLR3-X-EH.pdf)

[Digikey 1937-1145-ND](https://www.digikey.com/product-detail/en/io-audio-technologies/IO-XLR3-M-EH/1937-1145-ND/9931887)
[Datasheet](https://ioaudiotech.com/engineering-drawings/IO-XLR3-X-EH.pdf)

[Digikey 945-3158-ND](https://www.digikey.com/products/en?keywords=RFB-0505)
[Datasheet](https://recom-power.com/pdf/Econoline/RFB.pdf)

[NC5MAH Datasheet](https://www.neutrik.com/en/product/nc5mah.pdf)

[NC5FAH Datasheet](https://www.neutrik.com/en/product/nc5fah.pdf)

[NC3MAH Datasheet](https://www.neutrik.com/en/product/nc3mah.pdf)

[NC3FAH-0 Datasheet](https://www.neutrik.com/en/product/nc3fah-0.pdf)

## Isolation

There are a few different DMX Arduino shields but many of them do not have isolation as recommended by the USITT spec. The DMX-DD1 shamelessly steals it's design from [SparkFun ESP32 Thing Plus DMX to LED Shield](https://www.sparkfun.com/products/15110) which properly implements isolation including power supply isolation.

Additionally, the [mathertel.de DMX Shield for Arduino with isolation](http://www.mathertel.de/Arduino/DMXShield.aspx) properly implements isolation as well. In fact, the solder bridges in the DMX-DD1 design are modelled after the mathertel.de device, see the "Simplifying opportunities" section for using the mathertel.de with and without isolation as well as making is RDM-compatible.

Similarly, you can use the DMX-DD1 without isolation but leaving out the parts in the "optional" sections of the board and bridging 5 solder bridges (JP1-JP5) to bypass the isolation circuits.

## Other Options

[DFRobot DMX Shield for Arduino](https://www.dfrobot.com/product-984.html)
[mathertel.de DMX Shield for Arduino with isolation](http://www.mathertel.de/Arduino/DMXShield.aspx)

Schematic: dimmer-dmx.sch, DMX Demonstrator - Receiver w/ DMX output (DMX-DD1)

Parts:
A1: Arduino_UNO_R3; ARDUINO_R3_NO_HOLES
C2, C3, C4, C5: .01uF; CAP-PTH-2.54
D1: DATA; LED_D5.0mm
D2: CLOCK; LED_D5.0mm
D3: ERROR; LED_D5.0mm
D4: START_CODE; LED_D5.0mm
J1: Input; PinHeader_1x03_P2.54mm_Horizontal
J2: NC3FAH/NC5FAH; NEUTRIK-NC3FAH-NC5FAH
J3: NC3MAH/NC5MAH; NEUTRIK-NC3MAH-NC5MAH
R1, R2, R3, R4: 330; R_Axial_DIN0207_L6.3mm_D2.5mm_P10.16mm_Horizontal
R5, R6, R7, R8, R9, R10: 470; R_Axial_DIN0207_L6.3mm_D2.5mm_P10.16mm_Horizontal
R11, R13: 680; R_Axial_DIN0207_L6.3mm_D2.5mm_P10.16mm_Horizontal
R12: 120; R_Axial_DIN0207_L6.3mm_D2.5mm_P10.16mm_Horizontal
U1: NMA0505SC; Converter_DCDC_muRata_NMAxxxxSC_THT_Bypass
U2, U3, U4: 6N137; DIP-8_W7.62mm_Socket; MPN 6N137; Digi-Key_PN 160-1791-ND
U5: MAX3485CPA+; DIP-8_W7.62mm_Socket

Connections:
+5V: A1.5, C2.1, R1.1, R2.1, R3.1, R4.1, R5.1, U1.1 (VIN+), U2.8, U3.2, U4.2
/B: A1.22
/CLK: A1.23
/RX: A1.27, J1.3
/RXCLK: A1.28, J1.1
/~CLOCK: A1.14, D2.1
/~CLR: A1.24
/~DATA: A1.13, D1.1
/~DIM0: A1.26
/~DIM1: A1.25
/~DIM2: A1.21
/~DIM3: A1.20
/~ERR: A1.11, D3.1
/~SC: A1.12, D4.1
GND: A1.6, A1.7, A1.29, C2.2, J1.2, U1.2 (VIN-), U2.5
GNDD: C3.2, C4.2, C5.2, J2.1A, J2.1B, J3.1A, J3.1B, R13.2, U1.4 (VOUT-), U3.5, U4.5, U5.5 (GND)
unnamed: A1.15, R5.2, U2.6
unnamed: A1.16, R9.2
unnamed: A1.17, R7.2
unnamed: D1.2, R1.2
unnamed: D2.2, R2.2
unnamed: D3.2, R3.2
unnamed: D4.2, R4.2
unnamed: J2.2A, J2.2B, J3.2A, J3.2B, R12.1, R13.1, U5.7 (B)
unnamed: J2.3, J3.3, R11.1, R12.2, U5.6 (A)
unnamed: R6.1, U5.1 (RO)
unnamed: R6.2, U2.3
unnamed: R7.1, U3.3
unnamed: R8.1, U3.6, U5.2 (~RE), U5.3 (DE)
unnamed: R9.1, U4.3
unnamed: R10.1, U4.6, U5.4 (DI)
VDD: C3.1, C4.1, C5.1, R8.2, R10.2, R11.2, U1.6 (VOUT+), U2.2, U3.8, U4.8, U5.8 (VCC)

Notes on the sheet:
Connect pin 3 to 6 to bypass isolator
Connect J4 to J5 to bypass isolator
Connect pin 2 to 4 to bypass isolator

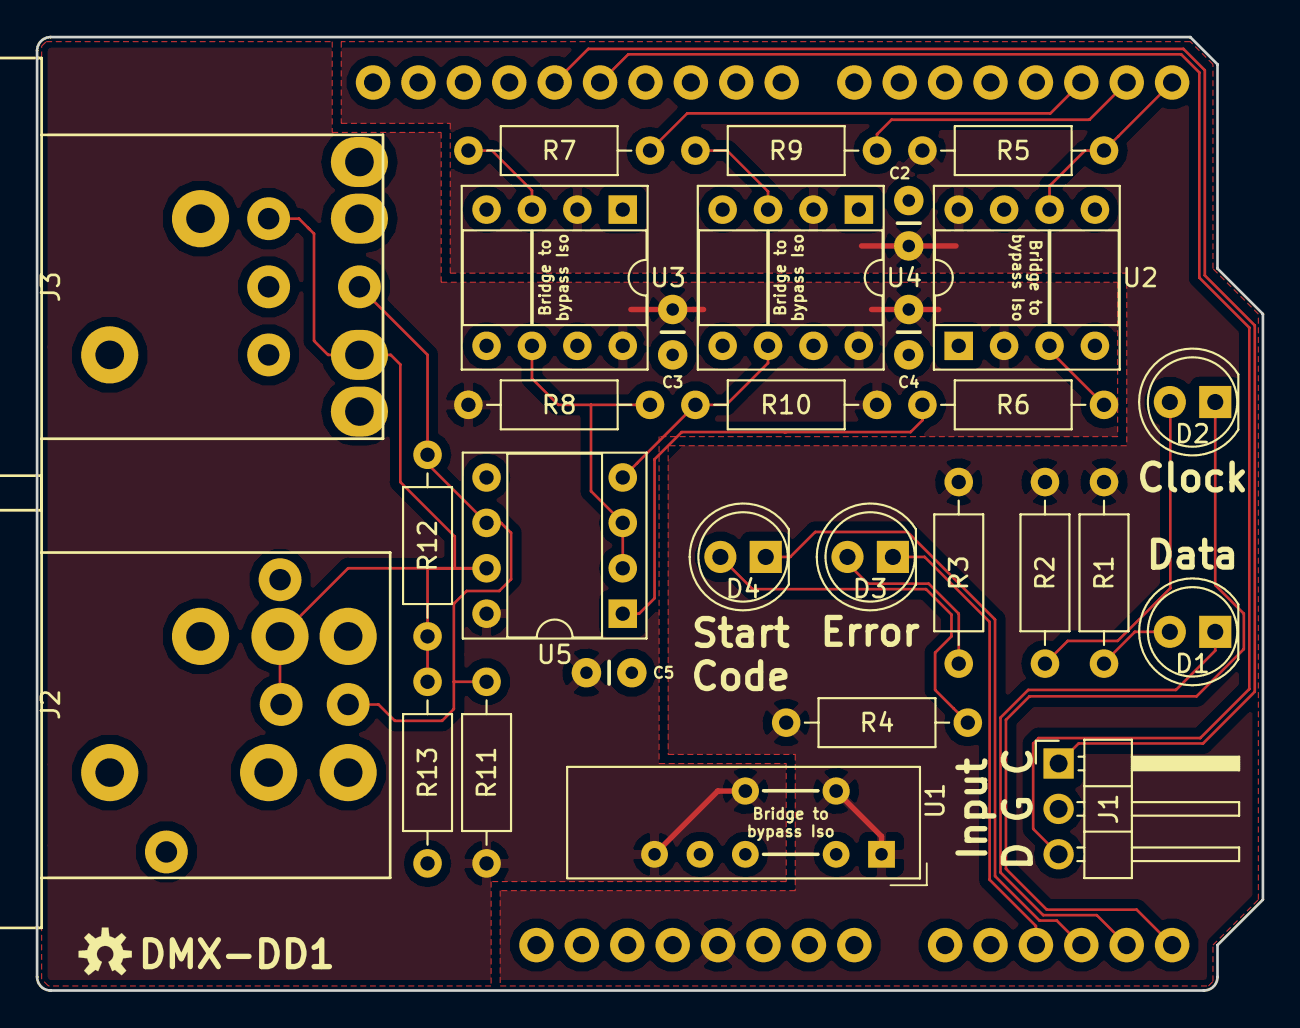
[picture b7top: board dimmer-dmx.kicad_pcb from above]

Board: 2 copper layers, 68.6 x 53.3 mm, 30 parts (0 on the bottom side), 25 nets.

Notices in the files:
hardware/control-pro/clock-control/clock-control.kicad_pcb:
Released under the Creative Commons Attribution Share-Alike 4.0m License
hardware/control-pro/transmitter/transmitter.kicad_pcb:
https://creativecommons.org/licenses/by-sa/4.0
Released under the Creative Commons Attribution Share-Alike 4.0 License
